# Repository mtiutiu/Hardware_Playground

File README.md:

# Hardware_Playground
Personal hardware designs.

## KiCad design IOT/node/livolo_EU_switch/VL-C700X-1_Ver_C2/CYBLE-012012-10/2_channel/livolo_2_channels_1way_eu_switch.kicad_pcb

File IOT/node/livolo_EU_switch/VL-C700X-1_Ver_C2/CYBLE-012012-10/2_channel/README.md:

## Mysensors PSOC PROC BLE (CYBLE-012012-10) Livolo 2 channels 1 way EU switch front module

##### 3D renderings of pcb

Top view | Bottom view
------------ | -------------
 | 

 **Kindly notice:**

The only thing I ask if using this project is to at least mention my name and if I don't ask too much you can also support my effort using the below button. Thanks for buying me a beer :).

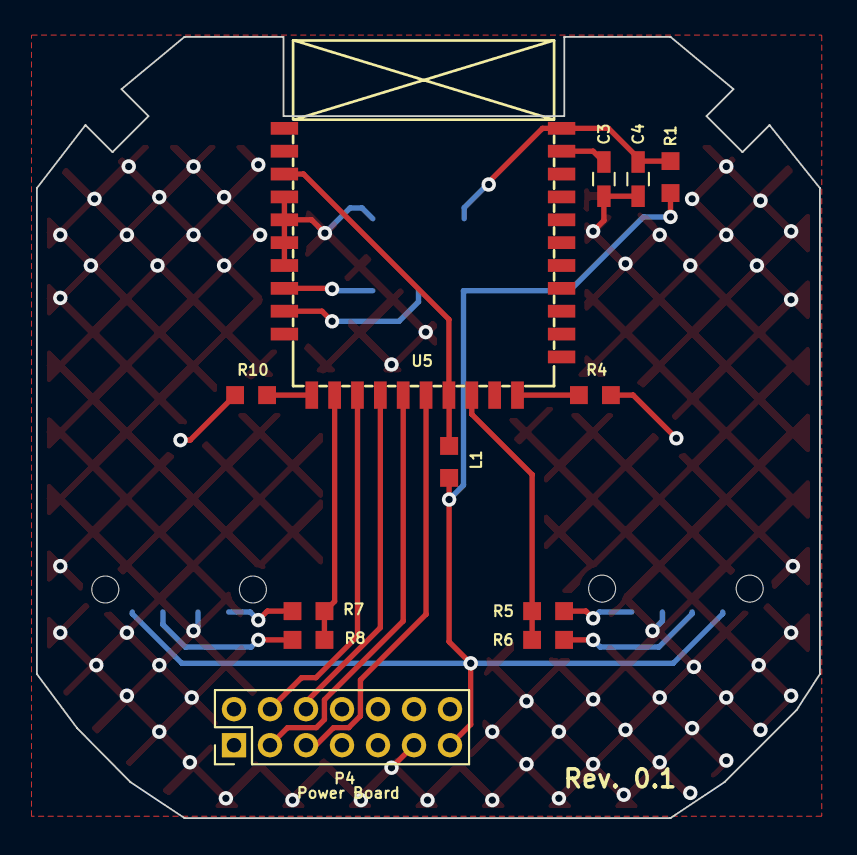
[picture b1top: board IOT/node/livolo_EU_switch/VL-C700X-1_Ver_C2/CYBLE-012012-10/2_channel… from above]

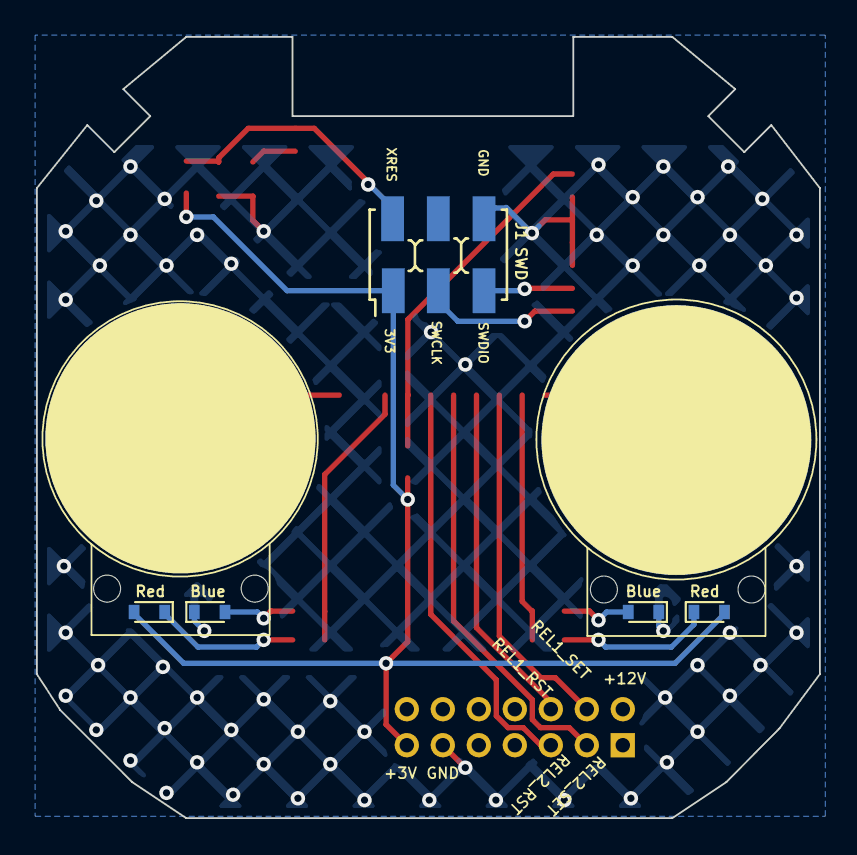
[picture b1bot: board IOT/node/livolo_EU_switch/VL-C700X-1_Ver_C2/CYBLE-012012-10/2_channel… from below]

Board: 2 copper layers, 43.5 x 43.4 mm, 19 parts (5 on the bottom side), 21 nets.

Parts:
C3: 2n2; C_0603_HandSoldering
C4: 100p; C_0603_HandSoldering
D3, D6: Blue; D_0603
D4, D5: Red; D_0603
J1: SWD; AVR_ISP_SMT_Small_02x03
L1: 300ohm/100Mhz; R_0603_1608Metric_Pad0.99x1.00mm_HandSolder
P4: Power Board; Pin_Header_Straight_2x07_Pitch2.00mm
R1, R4, R10: 4K7; R_0603_1608Metric_Pad0.99x1.00mm_HandSolder
R5, R6, R7, R8: 1K*; R_0603_1608Metric_Pad0.99x1.00mm_HandSolder
U1: Touch; livolo_ts_guard_cut_left
U5: CYBLE-012012-10
U6: Touch; livolo_ts_guard_cut_right

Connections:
+3V3: D4.2, D5.2, J1.1, L1.1, P4.13, R1.2
/Relay1_Reset: P4.6, U5.18
/Relay1_Set: P4.4, U5.19
/Relay2_Reset: P4.3, U5.17
/Relay2_Set: P4.5, U5.16
/S1_LEDs: R5.2, R6.2, U5.14
/S2_LEDs: R7.2, R8.2, U5.20
/SWCLK: J1.3, U5.23
/SWDIO: J1.5, U5.24
/TS1: R10.2, U5.21
/TS2: R4.1, U5.12
/XRES: C4.1, J1.2, R1.1, U5.1
GND: C3.1, C4.2, D3.1, D6.1, J1.6, P4.11, U5.25, U5.26, U5.27, U5.28
unnamed: C3.2, U5.2
unnamed: D3.2, R7.1
unnamed: D4.1, R8.1
unnamed: D5.1, R6.1
unnamed: D6.2, R5.1
unnamed: L1.2, U5.15, U5.29
unnamed: R4.2, U6.1
unnamed: R10.1, U1.1

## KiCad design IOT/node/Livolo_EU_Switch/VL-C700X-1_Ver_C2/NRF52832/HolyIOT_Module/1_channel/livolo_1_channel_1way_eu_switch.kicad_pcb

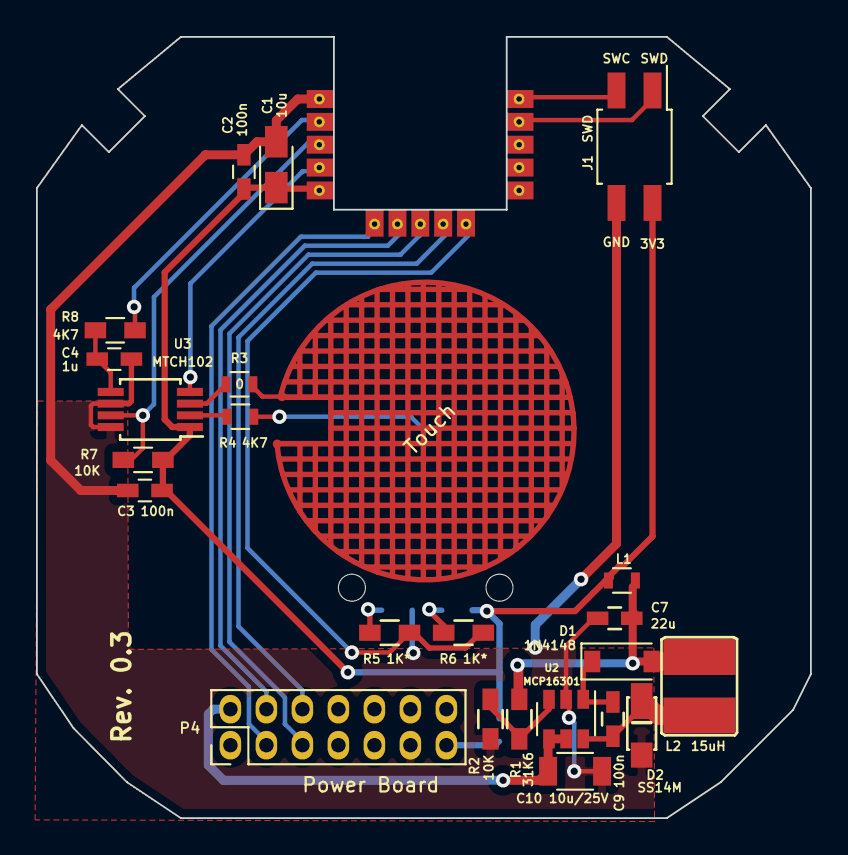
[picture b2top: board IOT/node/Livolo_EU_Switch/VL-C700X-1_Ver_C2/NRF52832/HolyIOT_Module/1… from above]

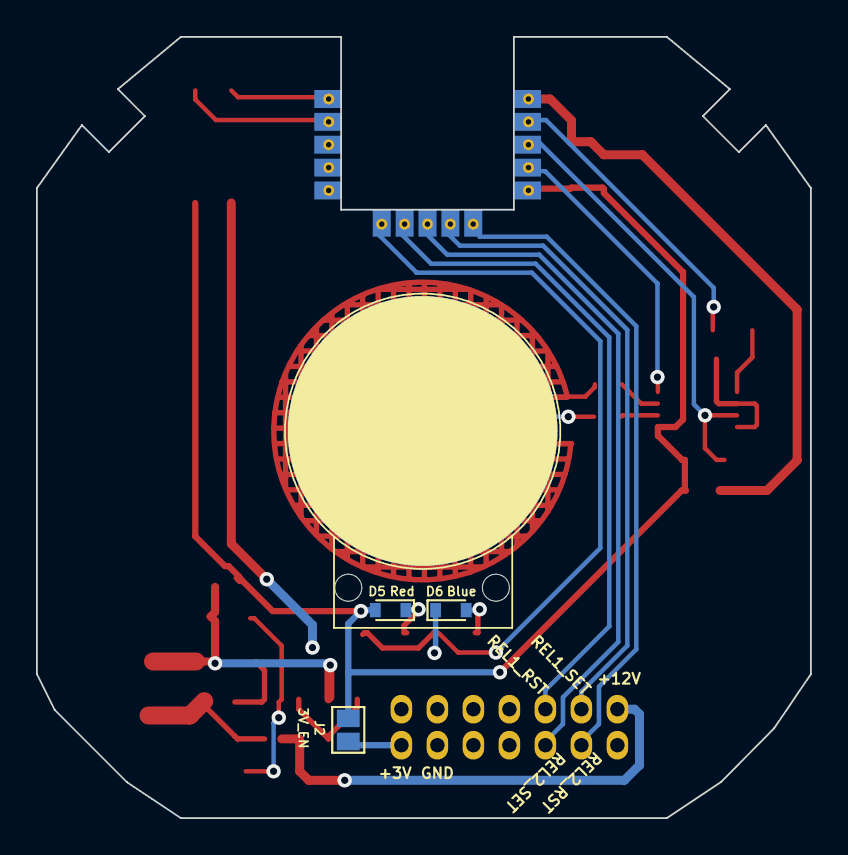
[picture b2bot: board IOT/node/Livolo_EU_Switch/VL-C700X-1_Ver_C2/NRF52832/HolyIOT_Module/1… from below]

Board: 2 copper layers, 43.0 x 43.4 mm, 28 parts (4 on the bottom side), 25 nets.

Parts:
C1: 10u; CP_Tantalum_Case-R_EIA-2012-12_Wave
C2, C3, C9: 100n; C_0603_HandSoldering
C4: 1u; C_0603_HandSoldering
C7: 22u; C_0603_HandSoldering
C10: 10u/25V; C_1206
D1: 1N4148; SOD-123
D2: SS14M
D5: Red; D_0603
D6: Blue; D_0603
J1: SWD; Pin_Header_Straight_2x02_Pitch2.00mm_SMD
J2: 3V_EN; GS2
L1: BLM18HE152SN1D; R_0603
L2: 15uH; VLCF4020T-150MR68
P4: Power Board; Pin_Header_Straight_2x07_Pitch2.00mm
R1: 31K6; R_0603_HandSoldering
R2, R7: 10K; R_0603_HandSoldering
R3: 0; R_0603
R4: 4K7; R_0603
R5, R6: 1K*; R_0603_HandSoldering
R8: 4K7; R_0603_HandSoldering
U1: Touch; livolo_ts_guard
U2: MCP16301; SOT-23-6
U3: MTCH102; MSOP-8_3x3mm_Pitch0.65mm
U5: H_NRF52832; Holyiot-NRF52832

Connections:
+3V3: C1.1, C2.2, C3.2, D5.2, J1.2, J2.1, L1.2, R7.2, U3.1, U5.5
/12Vcc: C10.1, P4.2, U2.4, U2.5
/MTPM: U3.4, U5.4
/MTSA: R8.1, U5.2
/Relay1_Reset: P4.6, U5.9
/Relay1_Set: P4.4, U5.7
/Relay2_Reset: P4.3, U5.6
/Relay2_Set: P4.5, U5.8
/S1_LEDs: R5.2, R6.2, U5.10
/SWCLK: J1.3, U5.15
/SWDIO: J1.1, U5.14
/TS1: R7.1, U3.7, U5.3
GND: C1.2, C2.1, C3.1, C4.2, C7.2, C10.2, D2.2, D6.1, J1.4, P4.11, R2.1, U2.2, U3.6, U3.8, U5.1
unnamed: C4.1, R8.2, U3.5
unnamed: C7.1, D1.2, L1.1, L2.1, R1.2
unnamed: C9.1, D1.1, U2.1
unnamed: C9.2, D2.1, L2.2, U2.6
unnamed: D5.1, R6.1
unnamed: D6.2, R5.1
unnamed: J2.2, P4.13
unnamed: R1.1, R2.2, U2.3
unnamed: R3.1, U3.3
unnamed: R3.2, U1.2
unnamed: R4.1, U3.2
unnamed: R4.2, U1.1

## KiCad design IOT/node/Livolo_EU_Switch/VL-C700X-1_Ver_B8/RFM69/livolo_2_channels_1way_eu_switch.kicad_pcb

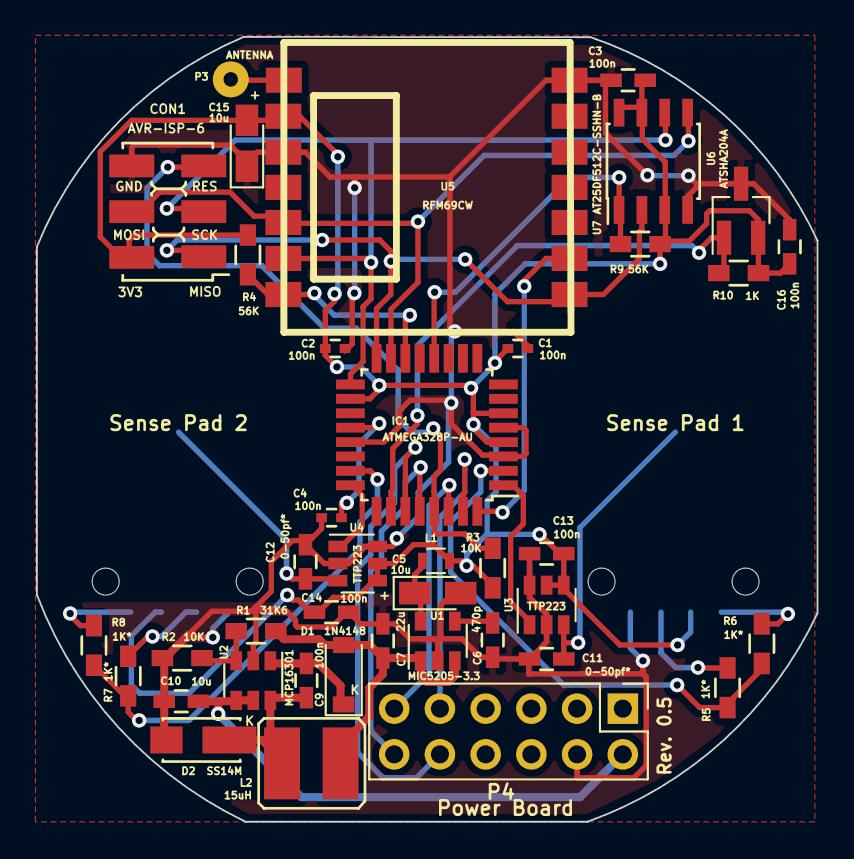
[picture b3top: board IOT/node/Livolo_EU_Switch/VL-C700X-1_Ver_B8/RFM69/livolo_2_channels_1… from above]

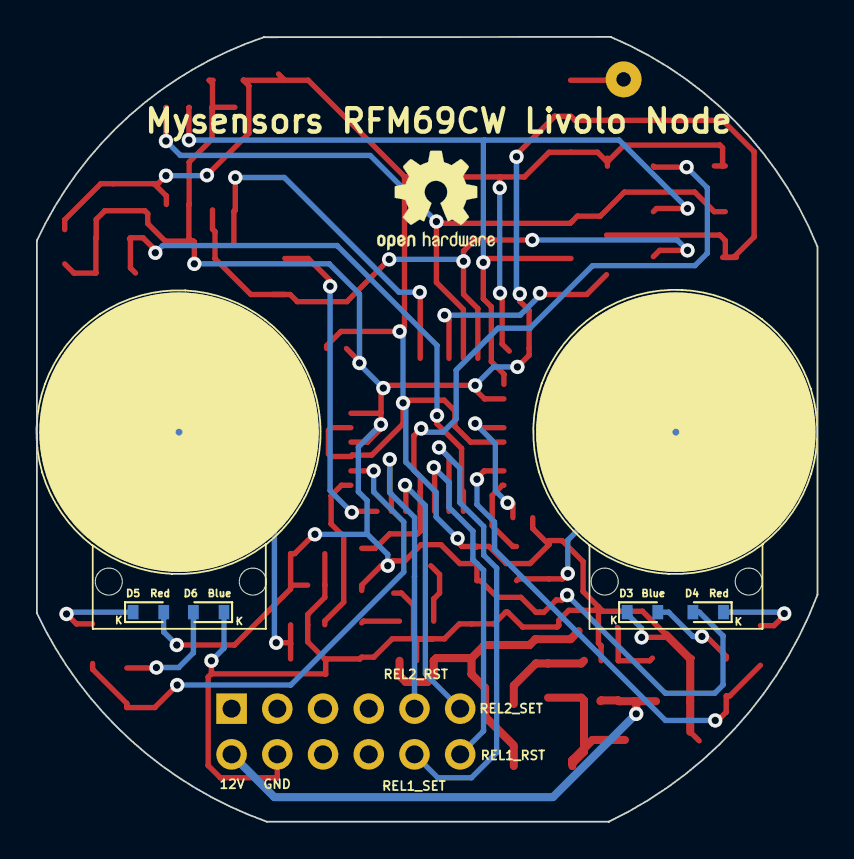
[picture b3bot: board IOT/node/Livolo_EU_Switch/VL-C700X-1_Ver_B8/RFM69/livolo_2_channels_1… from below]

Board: 2 copper layers, 43.4 x 43.6 mm, 46 parts (4 on the bottom side), 33 nets.

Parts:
C1, C2, C4: 100n; C_0402
C3, C9, C13, C14, C16: 100n; C_0603_HandSoldering
C5, C15: 10u; CP_Tantalum_Case-R_EIA-2012-12_Wave
C6: 470p; C_0603_HandSoldering
C7: 22u; C_0603_HandSoldering
C10: 10u; C_0603_HandSoldering
C11, C12: 0-50pf*; C_0603_HandSoldering
CON1: AVR-ISP-6; AVR_ISP_SMT_Small_02x03
D1: 1N4148; SOD-123
D2: SS14M
D3, D6: Blue; D_0603
D4, D5: Red; D_0603
IC1: ATMEGA328P-AU; TQFP-32_7x7mm_Pitch0.8mm
L1: BLM18HE152SN1D; R_0603
L2: 15uH; VLCF4020T-150MR68
P1: Sense Pad 1; touch_pad_16mm
P2: Sense Pad 2; touch_pad_16mm
P3: ANTENNA; SolderWirePad_single_0-8mmDrill
P4: Power Board; Pin_Header_Straight_2x06_Pitch2.54mm
R1: 31K6; R_0603_HandSoldering
R2, R3: 10K; R_0603_HandSoldering
R4, R9: 56K; R_0603_HandSoldering
R5, R6, R7, R8: 1K*; R_0603_HandSoldering
R10: 1K; R_0603_HandSoldering
U1: MIC5205-3.3; SOT-23-5
U2: MCP16301; SOT-23-6
U3, U4: TTP223; SOT-23-6
U5: RFM69CW
U6: AT25DF512C-SSHN-B; SOIC-8_3.9x4.9mm_Pitch1.27mm
U7: ATSHA204A; SOT-23_Handsoldering

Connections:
+3V3: C1.1, C2.2, C3.2, C13.1, C14.1, C15.2, C16.2, CON1.2, D4.2, D5.2, IC1.4, IC1.6, IC1.18, L1.1, R3.1, R4.2, R9.1, R10.1, U3.4, U3.5, U4.4, U4.5, U5.2, U6.3, U6.7, U6.8, U7.2
/12Vcc: C10.1, P4.2, U2.4, U2.5
/ATSHA204A: IC1.26, R10.2, U7.1
/FLASH_SS: IC1.12, R9.2, U6.1
/INT: IC1.32, U5.9
/MISO: CON1.1, IC1.16, U5.8, U6.2
/MOSI: CON1.4, IC1.15, U5.5, U6.5
/RADIO_SS: IC1.14, R4.1, U5.7
/RESET: CON1.5, IC1.29, R3.2
/Relay1_Reset: IC1.28, P4.12
/Relay1_Set: IC1.27, P4.10
/Relay2_Reset: IC1.31, P4.9
/Relay2_Set: IC1.30, P4.11
/S1_LEDs: IC1.2, R5.2, R6.2
/S2_LEDs: IC1.23, R7.2, R8.2
/SCK: CON1.3, IC1.17, U5.6, U6.6
/TS1: IC1.1, U3.1
/TS2: IC1.24, U4.1
GND: C1.2, C2.1, C3.1, C4.1, C5.2, C6.2, C7.2, C10.2, C11.2, C12.2, C13.2, C14.2, C15.1, C16.1, CON1.6, D2.2, D3.1, D6.1, IC1.3, IC1.5, IC1.21, P4.4, R2.1, U1.2, U2.2, U3.2, U3.6, U4.2, U4.6, U5.3, U5.14, U6.4, U7.3
unnamed: C4.2, IC1.20
unnamed: C5.1, L1.2, U1.5
unnamed: C6.1, U1.4
unnamed: C7.1, D1.2, L2.1, R1.2, U1.1, U1.3
unnamed: C9.1, D1.1, U2.1
unnamed: C9.2, D2.1, L2.2, U2.6
unnamed: C11.1, P1.1, U3.3
unnamed: C12.1, P2.1, U4.3
unnamed: D3.2, R7.1
unnamed: D4.1, R8.1
unnamed: D5.1, R6.1
unnamed: D6.2, R5.1
unnamed: P3.1, U5.1
unnamed: R1.1, R2.2, U2.3

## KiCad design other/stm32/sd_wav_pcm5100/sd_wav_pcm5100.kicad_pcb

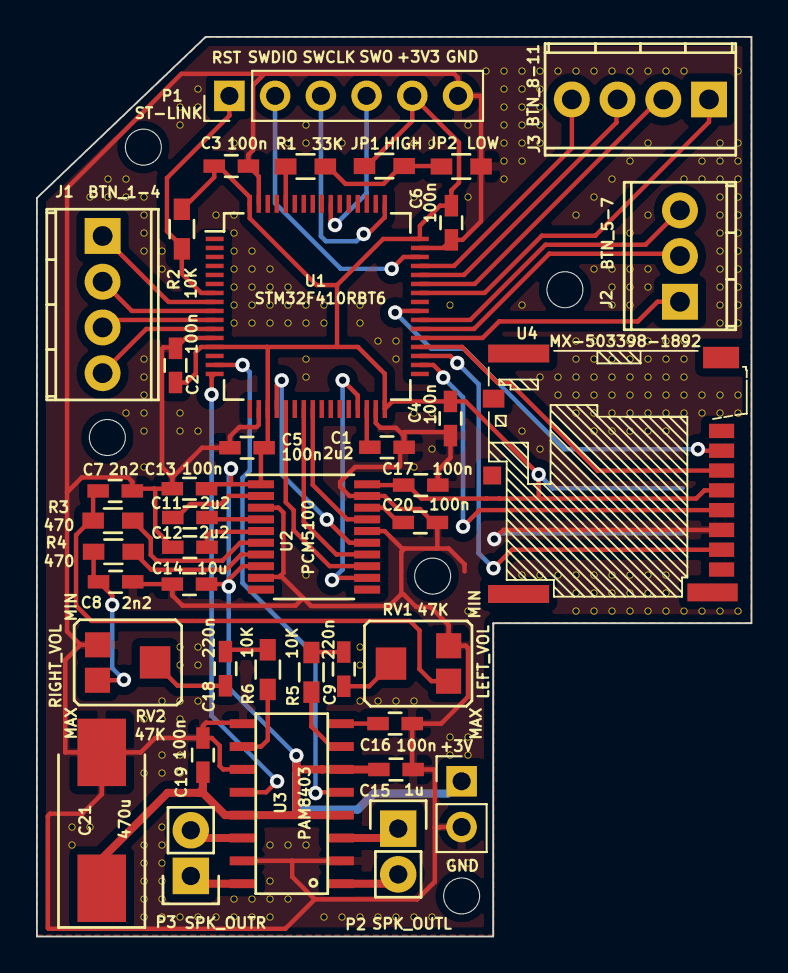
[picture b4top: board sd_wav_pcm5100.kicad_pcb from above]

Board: 2 copper layers, 39.7 x 50.0 mm, 323 parts (1 on the bottom side), 50 nets.

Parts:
C1, C11, C14: 2u2; C_0603_HandSoldering
C2, C3, C4, C5, C6, C13, C16, C17, C19, C20: 100n; C_0603_HandSoldering
C7, C8: 2n2; C_0603_HandSoldering
C9, C18: 220n; C_0603_HandSoldering
C10: 47u; C_0805_HandSoldering
C12: 10u; C_0603_HandSoldering
C15: 1u; C_0603_HandSoldering
C21: 470u; Tantalum_Case-D_EIA-7343-31_Hand
J1: BTN_1-4; TerminalBlock_Pheonix_MPT-2.54mm_4pol
J2: BTN_5-7; TerminalBlock_Pheonix_MPT-2.54mm_3pol
J3: BTN_8-11; TerminalBlock_Pheonix_MPT-2.54mm_4pol
JP1: HIGH; R_0603_HandSoldering
JP2: LOW; R_0603_HandSoldering
P1: ST-LINK; Pin_Header_Straight_1x06_Pitch2.54mm
P2: SPK_OUTL; Pin_Header_Straight_1x02
P3: SPK_OUTR; Pin_Header_Straight_1x02
P4: Supply; Pin_Header_Straight_1x02_Pitch2.54mm
R1: 33K; R_0603_HandSoldering
R2, R5, R6: 10K; R_0603_HandSoldering
R3, R4: 470; R_0603_HandSoldering
RV1, RV2: 47K; TC-33X-2
U1: STM32F410RBT6; LQFP-64_10x10mm_Pitch0.5mm
U2: PCM5100; TSSOP-20_4.4x6.5mm_Pitch0.65mm
U3: PAM8403; SOP16L
U4: MX-503398-1892
V2_44, V2_45, V3_9, V3_44, V4_8, V4_9, V5_8, V5_9, V5_21, V6_9, V6_10, V6_11, V6_12, V6_18, V6_19, V6_20, V6_21, V6_22, V6_24, V6_38, V6_41, V6_45, V6_46, V6_47, V6_48, V6_49, V7_12, V7_13, V7_37, V7_38, V7_40, V7_41, V7_44, V7_45, V7_46, V7_47, V7_48, V7_49, V8_4, V8_5, V8_21, V8_22, V8_34, V8_35, V8_37, V8_38, V8_40, V8_41, V8_49, V9_3, V9_4, V9_22, V9_34, V9_35, V9_37, V9_49, V10_10, V10_49, V11_6, V11_10, V11_11, V11_12, V11_13, V11_14, V11_15, V11_16, V11_48, V11_49, V12_12, V12_13, V12_14, V12_15, V12_16, V12_48, V12_49, V13_13, V13_14, V13_15, V13_16, V13_45, V13_47, V13_48, V13_49, V14_6, V14_14, V14_15, V14_16, V14_45, V14_48, V15_5, V15_6, V15_15, V15_16, V15_18, V15_19, V15_30, V15_45, V16_15, V16_16, V16_49, V17_6, V17_49, V18_15, V18_16, V18_34, V18_35, V18_37, V18_49, V19_17, V19_37, V19_49, V20_17, V20_18, V20_37, V20_49, V21_6, V21_9, V21_21, V21_24, V21_37, V21_49, V22_6, V22_21, V22_23, V22_49, V23_15, V23_39, V23_40, V23_46, V24_5, V24_9, V24_32, V24_39, V24_40, V24_46, V25_2, V26_2, V26_3, V26_4, V26_5, V26_6, V26_7, V26_8, V27_2, V27_3, V27_4, V27_5, V27_6, V27_7, V27_15, V27_22, V27_30, V28_2, V28_3, V28_4, V28_5, V28_6, V28_19, V28_23, V28_30, V29_2, V29_19, V29_20, V29_30, V30_2, V30_10, V30_17, V30_18, V30_19, V30_20, V30_21, V30_30, V30_31, V30_32, V31_2, V31_9, V31_13, V31_17, V31_18, V31_19, V31_20, V31_21, V31_22, V31_30, V31_31, V31_32, V32_2, V32_8, V32_13, V32_14, V32_15, V32_17, V32_18, V32_19, V32_20, V32_21, V32_22, V32_30, V32_31, V32_32, V33_2, V33_7, V33_11, V33_13, V33_14, V33_15, V33_17, V33_18, V33_19, V33_20, V33_21, V33_22, V33_30, V33_31, V33_32, V34_2, V34_6, V34_10, V34_13, V34_14, V34_17, V34_18, V34_19, V34_20, V34_21, V34_22, V34_30, V34_31, V34_32, V35_2, V35_17, V35_18, V35_19, V35_20, V35_21, V35_22, V35_30, V35_31, V35_32, V36_2, V36_8, V36_17, V36_18, V36_19, V36_20, V36_21, V36_32, V37_7, V37_8, V37_20, V37_21, V37_32, V38_6, V38_7, V38_8, V38_9, V38_10, V38_11, V38_12, V38_13, V38_14, V38_15, V38_16, V38_20, V38_21, V38_32, V39_2, V39_6, V39_7, V39_8, V39_9, V39_10, V39_11, V39_12, V39_13, V39_14, V39_15, V39_16, V39_20, V39_21, V39_32: AUTO_VIA; VIA_MATRIX

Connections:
+3V3: C2.1, C3.1, C4.1, C5.1, C6.1, C10.1, C12.2, C13.1, C15.2, C17.1, C19.1, C21.1, JP1.2, P1.5, P4.1, R2.2, U1.13, U1.19, U1.32, U1.48, U1.64, U2.1, U2.8, U2.20, U3.4, U3.6, U3.13, U4.4
/BTN1: J1.1, U1.8
/BTN2: J1.2, U1.9
/BTN3: J1.3, U1.10
/BTN4: J1.4, U1.11
/BTN5: J2.1, U1.37
/BTN6: J2.2, U1.38
/BTN7: J2.3, U1.39
/BTN8: J3.1, U1.42
/BTN9: J3.2, U1.43
/BTN10: J3.3, U1.44
/BTN11: J3.4, U1.45
/I2S_BCLK: U1.21, U2.13
/I2S_DATA: U1.23, U2.14
/I2S_LRCLK: U1.20, U2.15
/I2S_MCLK: U1.29, U2.12
/PAM8403_MUTE: U1.15, U3.5
/PAM8403_STANDBY: U1.16, U3.12
/PCM5100_MUTE: U1.24, U2.17
/PCM5100_OUTL: C7.2, R3.2, RV1.1
/PCM5100_OUTR: C8.2, R4.2, RV2.3
/SD_CS: U1.40, U4.2
/SD_DI: U1.36, U4.3
/SD_DO: U1.35, U4.7
/SD_SCLK: U1.34, U4.5
/SWCLK: P1.3, U1.49
/SWDIO: P1.2, U1.46
/SWO: P1.4, U1.55
/nRST: P1.1, R2.1, U1.7
GND: C1.2, C2.2, C3.2, C4.2, C5.2, C6.2, C7.1, C8.1, C10.2, C12.1, C13.2, C14.2, C15.1, C16.1, C17.2, C19.2, C20.2, C21.2, JP2.1, P1.6, P4.2, RV1.3, RV2.1, U1.12, U1.18, U1.31, U1.47, U1.63, U2.3, U2.9, U2.16, U2.19, U3.2, U3.9, U3.11, U3.15, U4.6, V2_44.1, V2_45.1, V3_9.1, V3_44.1, V4_8.1, V4_9.1, V5_8.1, V5_9.1, V5_21.1, V6_9.1, V6_10.1, V6_11.1, V6_12.1, V6_18.1, V6_19.1, V6_20.1, V6_21.1, V6_22.1, V6_24.1, V6_38.1, V6_41.1, V6_45.1, V6_46.1, V6_47.1, V6_48.1, V6_49.1, V7_12.1, V7_13.1, V7_37.1, V7_38.1, V7_40.1, V7_41.1, V7_44.1, V7_45.1, V7_46.1, V7_47.1, V7_48.1, V7_49.1, V8_4.1, V8_5.1, V8_21.1, V8_22.1, V8_34.1, V8_35.1, V8_37.1, V8_38.1, V8_40.1, V8_41.1, V8_49.1, V9_3.1, V9_4.1, V9_22.1, V9_34.1, V9_35.1, V9_37.1, V9_49.1, V10_10.1, V10_49.1, V11_6.1, V11_10.1, V11_11.1, V11_12.1, V11_13.1, V11_14.1, V11_15.1, V11_16.1, V11_48.1, V11_49.1, V12_12.1, V12_13.1, V12_14.1, V12_15.1, V12_16.1, V12_48.1, V12_49.1, V13_13.1, V13_14.1, V13_15.1, V13_16.1, V13_45.1, V13_47.1, V13_48.1, V13_49.1, V14_6.1, V14_14.1, V14_15.1, V14_16.1, V14_45.1, V14_48.1, V15_5.1, V15_6.1, V15_15.1, V15_16.1, V15_18.1, V15_19.1, V15_30.1, V15_45.1, V16_15.1, V16_16.1, V16_49.1, V17_6.1, V17_49.1, V18_15.1, V18_16.1, V18_34.1, V18_35.1, V18_37.1, V18_49.1, V19_17.1, V19_37.1, V19_49.1, V20_17.1, V20_18.1, V20_37.1, V20_49.1, V21_6.1, V21_9.1, V21_21.1, V21_24.1, V21_37.1, V21_49.1, V22_6.1, V22_21.1, V22_23.1, V22_49.1, V23_15.1, V23_39.1, V23_40.1, V23_46.1, V24_5.1, V24_9.1, V24_32.1, V24_39.1, V24_40.1, V24_46.1, V25_2.1, V26_2.1, V26_3.1, V26_4.1, V26_5.1, V26_6.1, V26_7.1, V26_8.1, V27_2.1, V27_3.1, V27_4.1, V27_5.1, V27_6.1, V27_7.1, V27_15.1, V27_22.1, V27_30.1, V28_2.1, V28_3.1, V28_4.1, V28_5.1, V28_6.1, V28_19.1, V28_23.1, V28_30.1, V29_2.1, V29_19.1, V29_20.1, V29_30.1, V30_2.1, V30_10.1, V30_17.1, V30_18.1, V30_19.1, V30_20.1, V30_21.1, V30_30.1, V30_31.1, V30_32.1, V31_2.1, V31_9.1, V31_13.1, V31_17.1, V31_18.1, V31_19.1, V31_20.1, V31_21.1, V31_22.1, V31_30.1, V31_31.1, V31_32.1, V32_2.1, V32_8.1, V32_13.1, V32_14.1, V32_15.1, V32_17.1, V32_18.1, V32_19.1, V32_20.1, V32_21.1, V32_22.1, V32_30.1, V32_31.1, V32_32.1, V33_2.1, V33_7.1, V33_11.1, V33_13.1, V33_14.1, V33_15.1, V33_17.1, V33_18.1, V33_19.1, V33_20.1, V33_21.1, V33_22.1, V33_30.1, V33_31.1, V33_32.1, V34_2.1, V34_6.1, V34_10.1, V34_13.1, V34_14.1, V34_17.1, V34_18.1, V34_19.1, V34_20.1, V34_21.1, V34_22.1, V34_30.1, V34_31.1, V34_32.1, V35_2.1, V35_17.1, V35_18.1, V35_19.1, V35_20.1, V35_21.1, V35_22.1, V35_30.1, V35_31.1, V35_32.1, V36_2.1, V36_8.1, V36_17.1, V36_18.1, V36_19.1, V36_20.1, V36_21.1, V36_32.1, V37_7.1, V37_8.1, V37_20.1, V37_21.1, V37_32.1, V38_6.1, V38_7.1, V38_8.1, V38_9.1, V38_10.1, V38_11.1, V38_12.1, V38_13.1, V38_14.1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
unnamed: C1.1, U1.30
unnamed: C9.1, R5.2
unnamed: C9.2, RV1.2
unnamed: C11.1, U2.4
unnamed: C11.2, U2.2
unnamed: C14.1, U2.5
unnamed: C16.2, U3.8
unnamed: C18.1, RV2.2
unnamed: C18.2, R6.1
unnamed: C20.1, U2.18
unnamed: JP1.1, JP2.2, R1.2
unnamed: P2.1, U3.3
unnamed: P2.2, U3.1
unnamed: P3.1, U3.16
unnamed: P3.2, U3.14
unnamed: R1.1, U1.60
unnamed: R3.1, U2.6
unnamed: R4.1, U2.7
unnamed: R5.1, U3.7
unnamed: R6.2, U3.10

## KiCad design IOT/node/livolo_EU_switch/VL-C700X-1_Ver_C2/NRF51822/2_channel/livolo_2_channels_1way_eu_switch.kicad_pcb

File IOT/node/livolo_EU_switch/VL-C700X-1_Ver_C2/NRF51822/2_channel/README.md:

## Mysensors NRF51822 Livolo 2 channels 1 way EU switch front module

##### 3D renderings of pcb

Top view | Bottom view
------------ | -------------
 | 

**Description:**

This is a Mysensors replica of the Livolo EU Switch(2 channels 1 way) front plate for the **VL-C702X-2_Ver_C1** Livolo hw revision.

**Key Features:**

 - **Capacitive touch sensing** using **MTCH105** specialized IC
 - **MySensors** ready(NRF51822)
 - **DC-DC Buck converter** for powering from the 12V line ( the DC-DC converter can be bypassed and not used at all if desired by soldering the **3V_EN** jumper and removing the L1 ferrite bead or by not soldering the dc-dc converter components)

**Firmware programming and testing steps for MySensors:**
1. Install Arduino IDE
2. Install nrf5 arduino core from here: https://github.com/sandeepmistry/arduino-nRF5
3. Select the **nrf51 generic board (16K ram and 256K flash)** variant(or nrf52 generic if you have a nrf52832 device)
4. The low frequency oscillator needs to be set to **RC oscillator** in the Arduino menu
5. **NO Softdevice** needs to be selected
6. Use a st-link v2 programmer
7. You need to connect only: SWD, SWCLK, Vdd and GND
8. Load your MySensors sketch or use the one provided with this project 

**Firmware programming and testing steps for BLE:**
1. Install Arduino IDE
2. Install nrf5 arduino core from here: https://github.com/sandeepmistry/arduino-nRF5
3. install Arduino ble peripheral library from here: https://github.com/sandeepmistry/arduino-BLEPeripheral
4. Install the required softdevice as explained here: https://github.com/sandeepmistry/arduino-nRF5#selecting-a-softdevice
5. Select the **nrf51 generic board (16K ram and 256K flash)** variant(or nrf52 generic if you have a nrf52832 device)
6. The low frequency oscillator needs to be set to **RC oscillator** in the Arduino menu
7. Select **S130** softdevice from menu if you have nrf51(or S132 if you have nrf52)
8. Use a st-link v2 programmer
9. You need to connect only: SWD, SWCLK, Vdd and GND
10. Load my BLE testing sketch, compile and upload
11. Use the nrf connect tool for Android: https://play.google.com/store/apps/details?id=no.nordicsemi.android.mcp&hl=en
12. Scan for available devices - you should see a "Livolo Lights" device
13. Connect to it
14. After connecting and characteristics discovery -> expand one of the "unknown characteristic"(there's one for each livolo channel or relay)
15. Use the button with an UP arrow on it to send values - select **UINT8** - send 1 for turning ON the light, send 0 for turning OFF the light for the selected channel

**Extra steps needed for the Livolo power supply/relays board!!!**
 1. The R3 resistor(marked with 104 - 100Kohm) near the bridge rectifier needs to be replaced with a 1Kohm one(1206 package)
 2. The R13 SMD resistor needs to be replaced with a solder bridge
 3. Mount a X2 capacitor of 1uF - 2.2uF rated at a minimum of 275Vac directly on the light bulb(in parallel)

**Notes:**
 - If using BLE based firmware with this board the current consumption on average is only **5mA **for the **WHOLE BOARD**(including leds) and this is **constant** over time
 - If using MySensors firmware instead the current consumption on average increases to **18-20mA **which is 4 times bigger than BLE
 - What I noticed is that the original Livolo power supply(the one used in stand-by mode) is designed to work with currents of 1mA or even below so that's why the above hardware modifications(the extra steps) need to be performed - otherwise the switch won't start
 - It's not advised to replace the R3 resistor with a bridge only as the stand-by power supply may be damaged over time and it's required that the custom top board(for which the current project was made for) to draw a lower current as much as possible(ideally would be several milliamps and even lower but it works with 10-20mA also)

**Practical usage ideas:**
 - Currently(and based on my previous experience with this kind of project) I will use all the Livolo switches preloaded with BLE firmware because of the lower current consumption AND in each room there will be a BLE Central node(based on Raspberry PI Zero W) - see this project: [RFM69W Raspberry PI Zero(W) Shield(HAT)](https://www.openhardware.io/view/487/RFM69W-Raspberry-PI-ZeroW-ShieldHAT) which will route messages to/from the Livolo switches BLE Peripherals to the MySensors network.

**HW Revisions:**
 - 0.1 - initial hw design
 - 0.2 - switched to MTCH105 touch sensor
 - 0.3 - added 3V line jumper

**Kindly notice:**

The only thing I ask if using this project is to at least mention my name and if I don't ask too much you can also support my effort using the below button. Thanks for buying me a beer :).

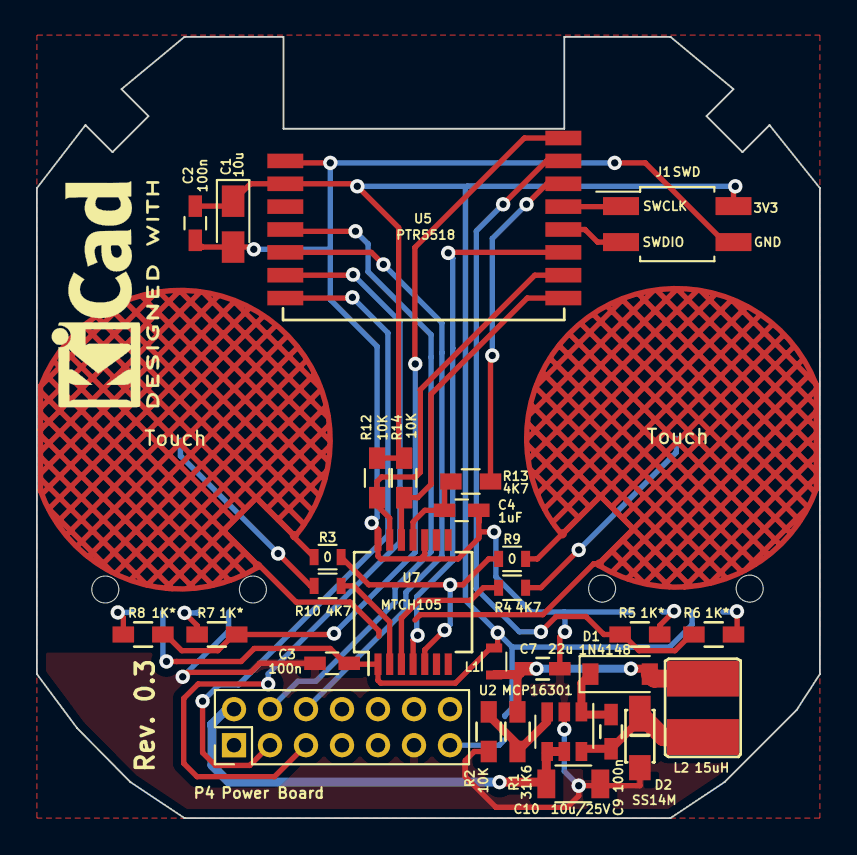
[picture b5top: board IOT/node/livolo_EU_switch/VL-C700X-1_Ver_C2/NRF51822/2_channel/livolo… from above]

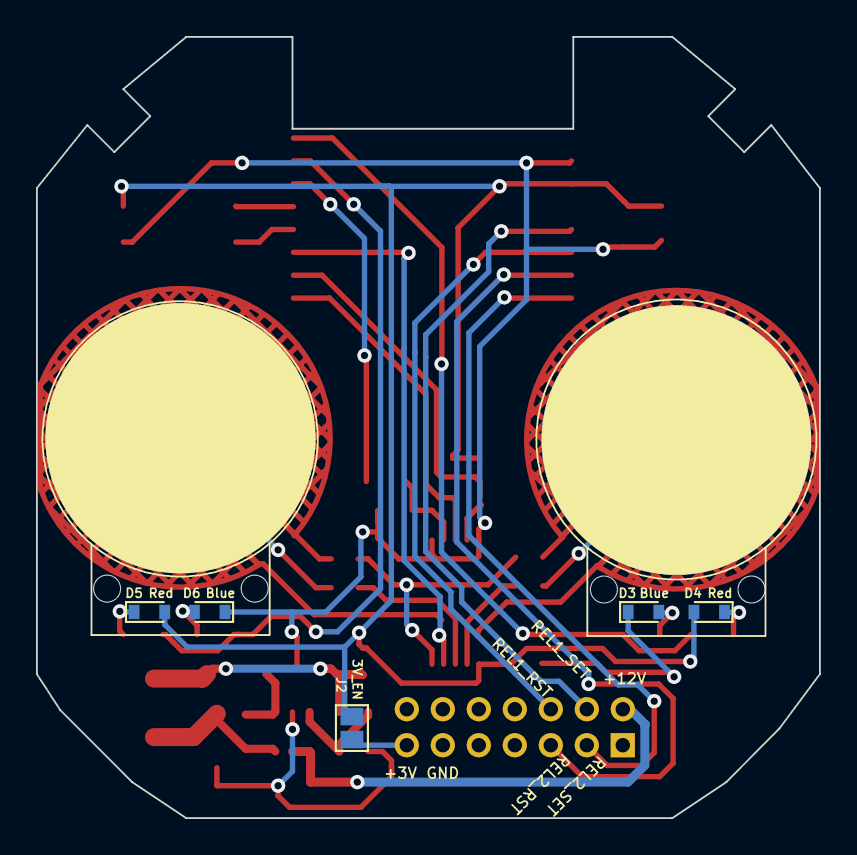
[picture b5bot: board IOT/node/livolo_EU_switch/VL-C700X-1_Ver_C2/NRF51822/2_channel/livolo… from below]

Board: 2 copper layers, 43.5 x 43.4 mm, 36 parts (5 on the bottom side), 32 nets.

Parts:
C1: 10u; CP_Tantalum_Case-R_EIA-2012-12_Wave
C2, C3, C9: 100n; C_0603_HandSoldering
C4: 1uF; C_0603_HandSoldering
C7: 22u; C_0603_HandSoldering
C10: 10u/25V; C_1206
D1: 1N4148; SOD-123
D2: SS14M
D3, D6: Blue; D_0603
D4, D5: Red; D_0603
J1: SWD; Pin_Header_Straight_2x02_Pitch2.00mm_SMD
J2: 3V_EN; GS2
L1: BLM18HE152SN1D; R_0603
L2: 15uH; VLCF4020T-150MR68
P4: Power Board; Pin_Header_Straight_2x07_Pitch2.00mm
R1: 31K6; R_0603_HandSoldering
R2, R12, R14: 10K; R_0603_HandSoldering
R3, R9: 0; R_0603
R4, R10: 4K7; R_0603
R5, R6, R7, R8: 1K*; R_0603_HandSoldering
R13: 4K7; R_0603_HandSoldering
U1: Touch; livolo_ts_guard_cut_left
U2: MCP16301; SOT-23-6
U5: PTR5518
U6: Touch; livolo_ts_guard_cut_right
U7: MTCH105; SSOP-14_5.3x6.2mm_Pitch0.65mm

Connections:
+3V3: C1.1, C2.2, C3.1, D4.2, D5.2, J1.2, J2.2, L1.2, R12.1, R14.1, U5.10, U7.1
/12Vcc: C10.1, P4.2, U2.4, U2.5
/MTPM: U5.3, U7.4
/MTSA: R13.1, U5.6
/Relay1_Reset: P4.6, U5.13
/Relay1_Set: P4.4, U5.12
/Relay2_Reset: P4.3, U5.15
/Relay2_Set: P4.5, U5.14
/S1_LEDs: R5.2, R6.2, U5.7
/S2_LEDs: R7.2, R8.2, U5.8
/SWCLK: J1.1, U5.5
/SWDIO: J1.3, U5.4
/TS1: R12.2, U5.2, U7.13
/TS2: R14.2, U5.1, U7.12
GND: C1.2, C2.1, C3.2, C4.1, C7.2, C10.2, D2.2, D3.1, D6.1, J1.4, P4.11, R2.1, U2.2, U5.9, U7.10, U7.14
unnamed: C4.2, R13.2, U7.11
unnamed: C7.1, D1.2, L1.1, L2.1, R1.2
unnamed: C9.1, D1.1, U2.1
unnamed: C9.2, D2.1, L2.2, U2.6
unnamed: D3.2, R7.1
unnamed: D4.1, R8.1
unnamed: D5.1, R6.1
unnamed: D6.2, R5.1
unnamed: J2.1, P4.13
unnamed: R1.1, R2.2, U2.3
unnamed: R3.1, U1.2
unnamed: R3.2, R9.1, U7.5
unnamed: R4.1, U7.3
unnamed: R4.2, U6.1
unnamed: R9.2, U6.2
unnamed: R10.1, U1.1
unnamed: R10.2, U7.2

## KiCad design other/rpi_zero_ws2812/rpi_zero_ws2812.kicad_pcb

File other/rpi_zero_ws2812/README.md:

## Raspberry Pi Zero(W) WS28xx Shield(HAT)

##### 3D renderings of pcb

Top view | Bottom view
------------ | -------------
 | 

**Description:**

This is a WS28xx shield(or HAT) for the Raspberry Pi Zero(W) Linux SBC

**Key Features:**

 - **DS18B20** temperature/humidity sensor
 - **Power connectors** for the WS28xx led strip
 - **Level shifter** for the WS28xx led strip

**HW Revisions:**
 - 0.1 - initial design

The only thing I ask if using this project is to at least mention my name and if I don't ask too much you can also support my effort using the below button. Thanks.

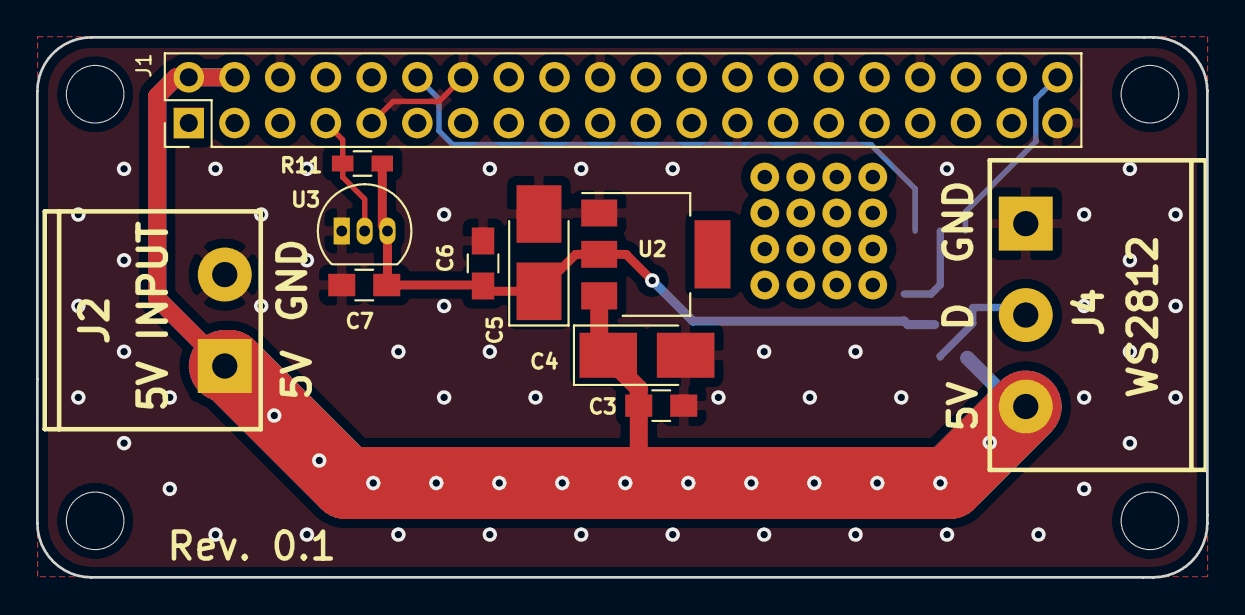
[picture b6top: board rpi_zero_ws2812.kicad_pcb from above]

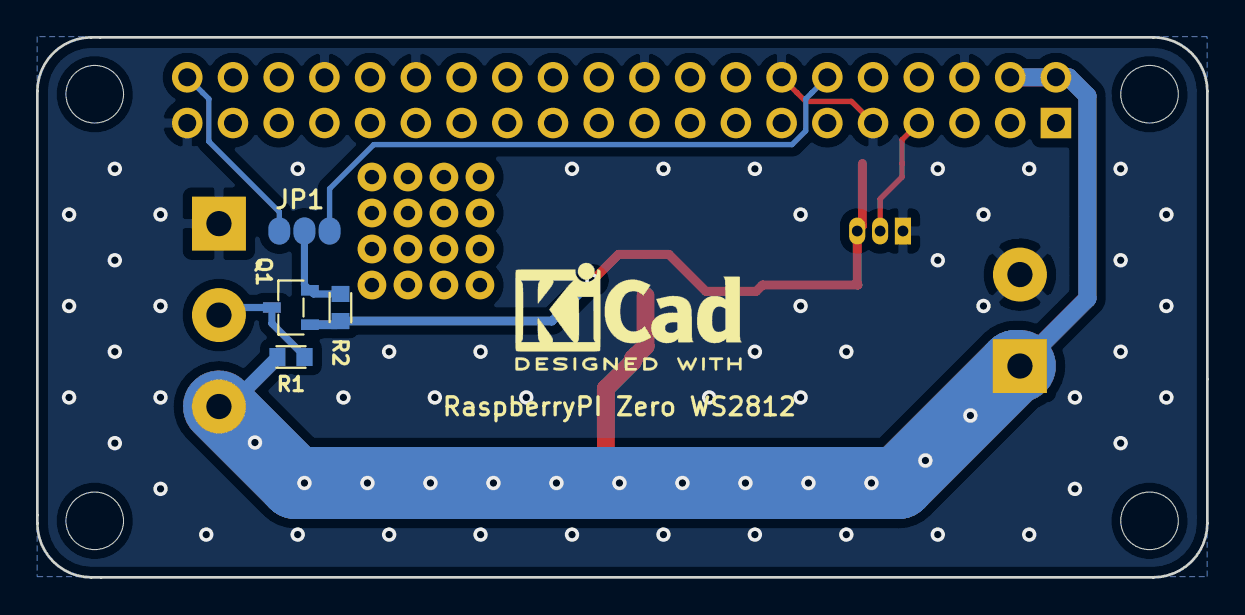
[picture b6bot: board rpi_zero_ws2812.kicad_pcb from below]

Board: 2 copper layers, 65.0 x 30.0 mm, 15 parts (4 on the bottom side), 8 nets.

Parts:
C3, C6, C7: 100n; C_0805_HandSoldering
C4, C5: 22u; CP_Tantalum_Case-B_EIA-3528-21_Hand
J1: RPI_Zero; Pin_Header_Straight_2x20_Pitch2.54mm
J2: 5V INPUT; mstba_2,5%2f2-g-5,08
J4: WS2812; mstba_2,5%2f3-g-5,08
JP1: ws2812_data_sel; 3_pin_solder_jumper_smd
Q1: BSS138; sot23
R1, R2: 10K; r_0603
R11: 4K7; R_0603_HandSoldering
U2: AMS1117; SOT-223
U3: DS18B20; TO-92_Inline_Narrow_Oval

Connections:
+3V3: C5.1, C6.2, C7.1, Q1.1, R2.2, R11.1, U2.2, U3.3
+5V: C3.2, C4.1, J1.2, J1.4, J2.1, J4.3, R1.1, U2.3
/TEMP_SENS: J1.7, R11.2, U3.2
/WS2812_DIN: JP1.2, Q1.3, R2.1
/WS2812_DOUT: J4.2, Q1.2, R1.2
/WS2812_PCM: J1.40, JP1.1
/WS2812_PWM: J1.12, JP1.3
GND: C3.1, C4.2, C5.2, C6.1, C7.2, J1.6, J1.9, J1.14, J1.20, J1.25, J1.30, J1.34, J1.39, J2.2, J4.1, U2.1, U3.1

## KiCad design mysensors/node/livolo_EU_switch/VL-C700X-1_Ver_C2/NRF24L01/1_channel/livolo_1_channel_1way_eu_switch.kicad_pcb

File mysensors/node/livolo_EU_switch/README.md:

## Mysensors RFM69 Livolo 2 ways EU switch front module
More details here: https://www.openhardware.io/view/306

##### 3D renderings of pcb

Top view | Bottom view
------------ | -------------
 | 

**Description:**

This is a Mysensors replica of the Livolo EU Switch(2 ways) front plate. 

**Key Features:**

 - **Capacitive touch sensing** using **TTP223** specialized IC
 - **AT25DF512C-SSHN-B** SPI flash module for OTA
 - **ATSHA204A** for signing
 - **MySensors** ready(Atmega328p + RFM69CW)
 - **DC-DC Buck converter** in combination with a **linear LDO voltage regulator** for efficient **noise cancelling**
  (the used LDO reduces a little bit the Buck's converter current capability - down to 150mA from 600mA but this is not important as the whole board takes about 60mA at peak)

**Work progress:**
 1. Identify the 12V line from the Livolo power/relays board - **DONE**
 2. Add **AT25DF512C-SSHN-B** SPI Flash module for OTA and **ATSHA204A** for signing - **DONE**
 3. Test/verify the pcb board correctness(from both electrical and mechanical point of views) - **DONE**
 4. Produce the initial PCB's using some external PCB manufacturer - **DONE**
 5. Components assembly(soldering) - **DONE**
 6. Create Mysensors sketch code - **DONE**
 7. Verify the real board with running code - **DONE**
 8. Verify OTA - **DONE**

Regarding point 1. from above: the EU variant that I have(VL-C700X-1 Ver: B8) doesn't expose the 12V line unfortunately. So I see 2 options here:

1. Bypass the 3V regulator from the power supply/relays board completely so that I get 12V directly to my board
2. ~~Find a free(if available) pin on the 2x6 pin connector and solder a wire to that pin from the 12V line(this requires less intervention)~~

One another thing that I noticed is that the relays are bistable so I modified the schematic/pcb to accommodate that(the relays used on my livolo switch are: **HFE60 12-1HST-L2** ( **2 coils latching, 1 Form A** as per datasheet: http://www.hongfa.com/pro/pdf/HFE60_en.pdf).

**HW Revisions:**
 - 0.1 - added SPI flash for OTA and signing support
 - 0.2 - fixed SPI slave select lines for flash and radio module
 - 0.3 - added ATSHA204A pull-up resistor
 - 0.4 - fixed leds orientation and added touch pads silkscreen
 - 0.5 - added tantalum caps for better power supply and radio stability(removed MCU reset pin cap)
 
**Credits:**
  
  All credits go to **MySensors** team for the great work and to the opensource community

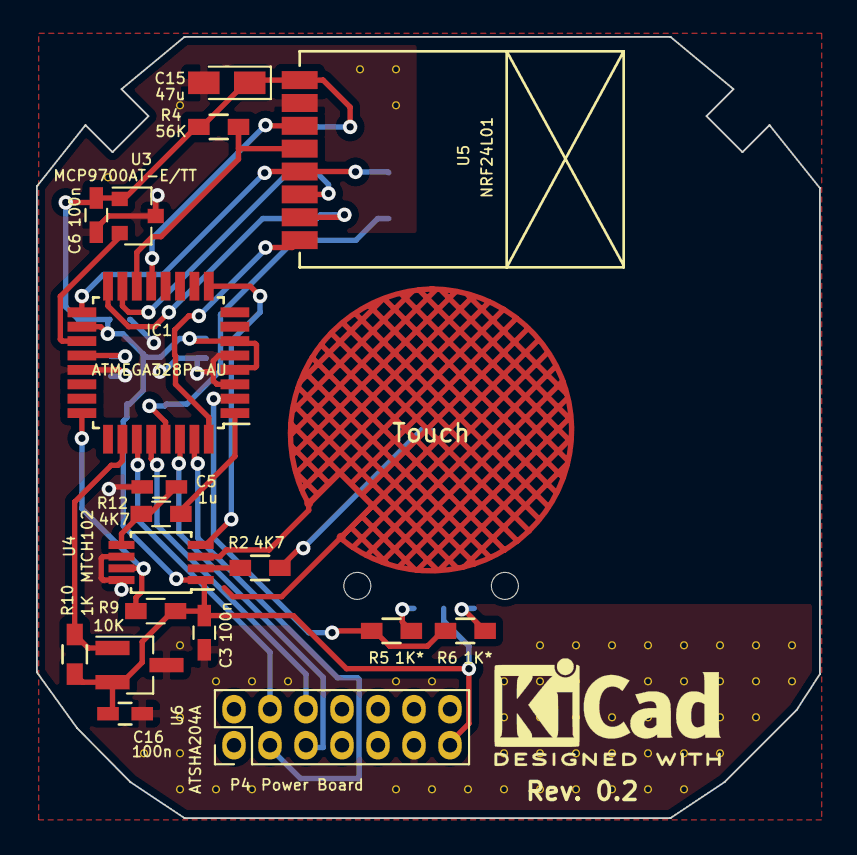
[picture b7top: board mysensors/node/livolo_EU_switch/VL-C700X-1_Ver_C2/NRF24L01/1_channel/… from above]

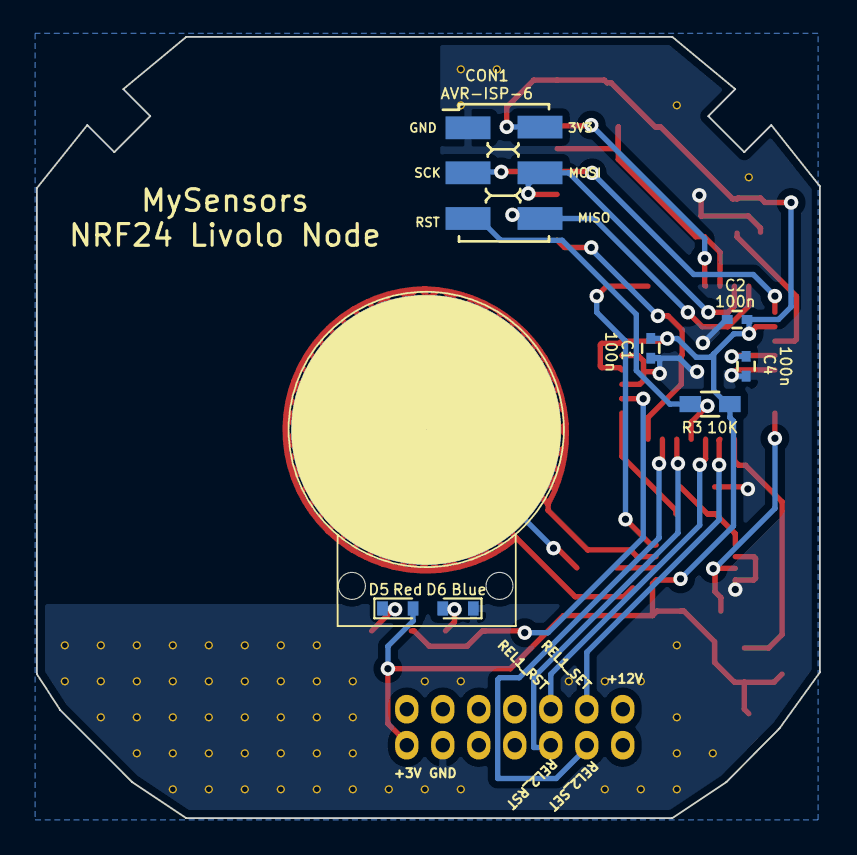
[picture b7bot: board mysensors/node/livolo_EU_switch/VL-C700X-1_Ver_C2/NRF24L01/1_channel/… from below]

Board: 2 copper layers, 43.5 x 43.4 mm, 84 parts (7 on the bottom side), 26 nets.

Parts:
C1, C2, C4: 100n; C_0402
C3, C6, C16: 100n; C_0603_HandSoldering
C5: 1u; C_0603_HandSoldering
C15: 47u; CP_Tantalum_Case-R_EIA-2012-12_Wave
CON1: AVR-ISP-6; AVR_ISP_SMT_Small_02x03
D5: Red; D_0603
D6: Blue; D_0603
IC1: ATMEGA328P-AU; TQFP-32_7x7mm_Pitch0.8mm
P4: Power Board; Pin_Header_Straight_2x07_Pitch2.00mm
R2, R12: 4K7; R_0603_HandSoldering
R3, R9: 10K; R_0603_HandSoldering
R4: 56K; R_0603_HandSoldering
R5, R6: 1K*; R_0603_HandSoldering
R10: 1K; R_0603_HandSoldering
U1: Touch; livolo_ts_guard_cut_simple
U3: MCP9700AT-E/TT; SOT-23
U4: MTCH102; MSOP-8_3x3mm_Pitch0.65mm
U5: NRF24L01; NRF24L01-SMD
U6: ATSHA204A; SOT-23_Handsoldering
V2_4, V3_20, V4_2, V4_17, V4_19, V4_20, V4_21, V5_18, V5_21, V6_18, V6_21, V7_18, V9_1, V10_1, V10_2, V10_18, V10_21, V11_18, V11_21, V12_21, V13_18, V13_19, V13_20, V13_21, V14_17, V14_18, V14_19, V14_20, V14_21, V15_17, V15_18, V15_19, V15_20, V15_21, V16_17, V16_18, V16_19, V16_20, V16_21, V17_17, V17_18, V17_19, V17_20, V17_21, V18_17, V18_18, V18_19, V18_20, V18_21, V19_17, V19_18, V19_19, V19_20, V20_17, V20_18, V20_19, V21_17, V21_18: AUTO_VIA; VIA_MATRIX

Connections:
+3V3: C1.1, C2.2, C3.1, C6.2, C15.1, C16.2, CON1.2, D5.2, IC1.4, IC1.6, IC1.18, P4.13, R3.1, R4.2, R9.1, R10.1, U3.1, U4.1, U5.2, U6.2
/ATSHA204A: IC1.26, R10.2, U6.1
/MISO: CON1.6, IC1.16, U5.7
/MOSI: CON1.4, IC1.15, U5.6
/MTPM: IC1.9, U4.4
/MTSA: IC1.1, R12.1
/RADIO_CE: IC1.13, U5.3
/RADIO_CSN: IC1.14, R4.1, U5.4
/RADIO_IRQ: IC1.32, U5.8
/RESET: CON1.5, IC1.29, R3.2
/Relay1_Reset: IC1.28, P4.6
/Relay1_Set: IC1.27, P4.4
/Relay2_Reset: IC1.31, P4.3
/Relay2_Set: IC1.30, P4.5
/S1_LEDs: IC1.2, R5.2, R6.2
/SCK: CON1.3, IC1.17, U5.5
/TEMP_SENS: IC1.19, U3.2
/TS1: IC1.24, R9.2, U4.7
GND: C1.2, C2.1, C3.2, C4.1, C5.2, C6.1, C15.2, C16.1, CON1.1, D6.1, IC1.3, IC1.5, IC1.21, P4.11, U3.3, U4.6, U4.8, U5.1, U6.3, V2_4.1, V3_20.1, V4_2.1, V4_17.1, V4_19.1, V4_20.1, V4_21.1, V5_18.1, V5_21.1, V6_18.1, V6_21.1, V7_18.1, V9_1.1, V10_1.1, V10_2.1, V10_18.1, V10_21.1, V11_18.1, V11_21.1, V12_21.1, V13_18.1, V13_19.1, V13_20.1, V13_21.1, V14_17.1, V14_18.1, V14_19.1, V14_20.1, V14_21.1, V15_17.1, V15_18.1, V15_19.1, V15_20.1, V15_21.1, V16_17.1, V16_18.1, V16_19.1, V16_20.1, V16_21.1, V17_17.1, V17_18.1, V17_19.1, V17_20.1, V17_21.1, V18_17.1, V18_18.1, V18_19.1, V18_20.1, V18_21.1, V19_17.1, V19_18.1, V19_19.1, V19_20.1, V20_17.1, V20_18.1, V20_19.1, V21_17.1, V21_18.1
unnamed: C4.2, IC1.20
unnamed: C5.1, R12.2, U4.5
unnamed: D5.1, R6.1
unnamed: D6.2, R5.1
unnamed: R2.1, U1.1
unnamed: R2.2, U4.2
unnamed: U1.2, U4.3
